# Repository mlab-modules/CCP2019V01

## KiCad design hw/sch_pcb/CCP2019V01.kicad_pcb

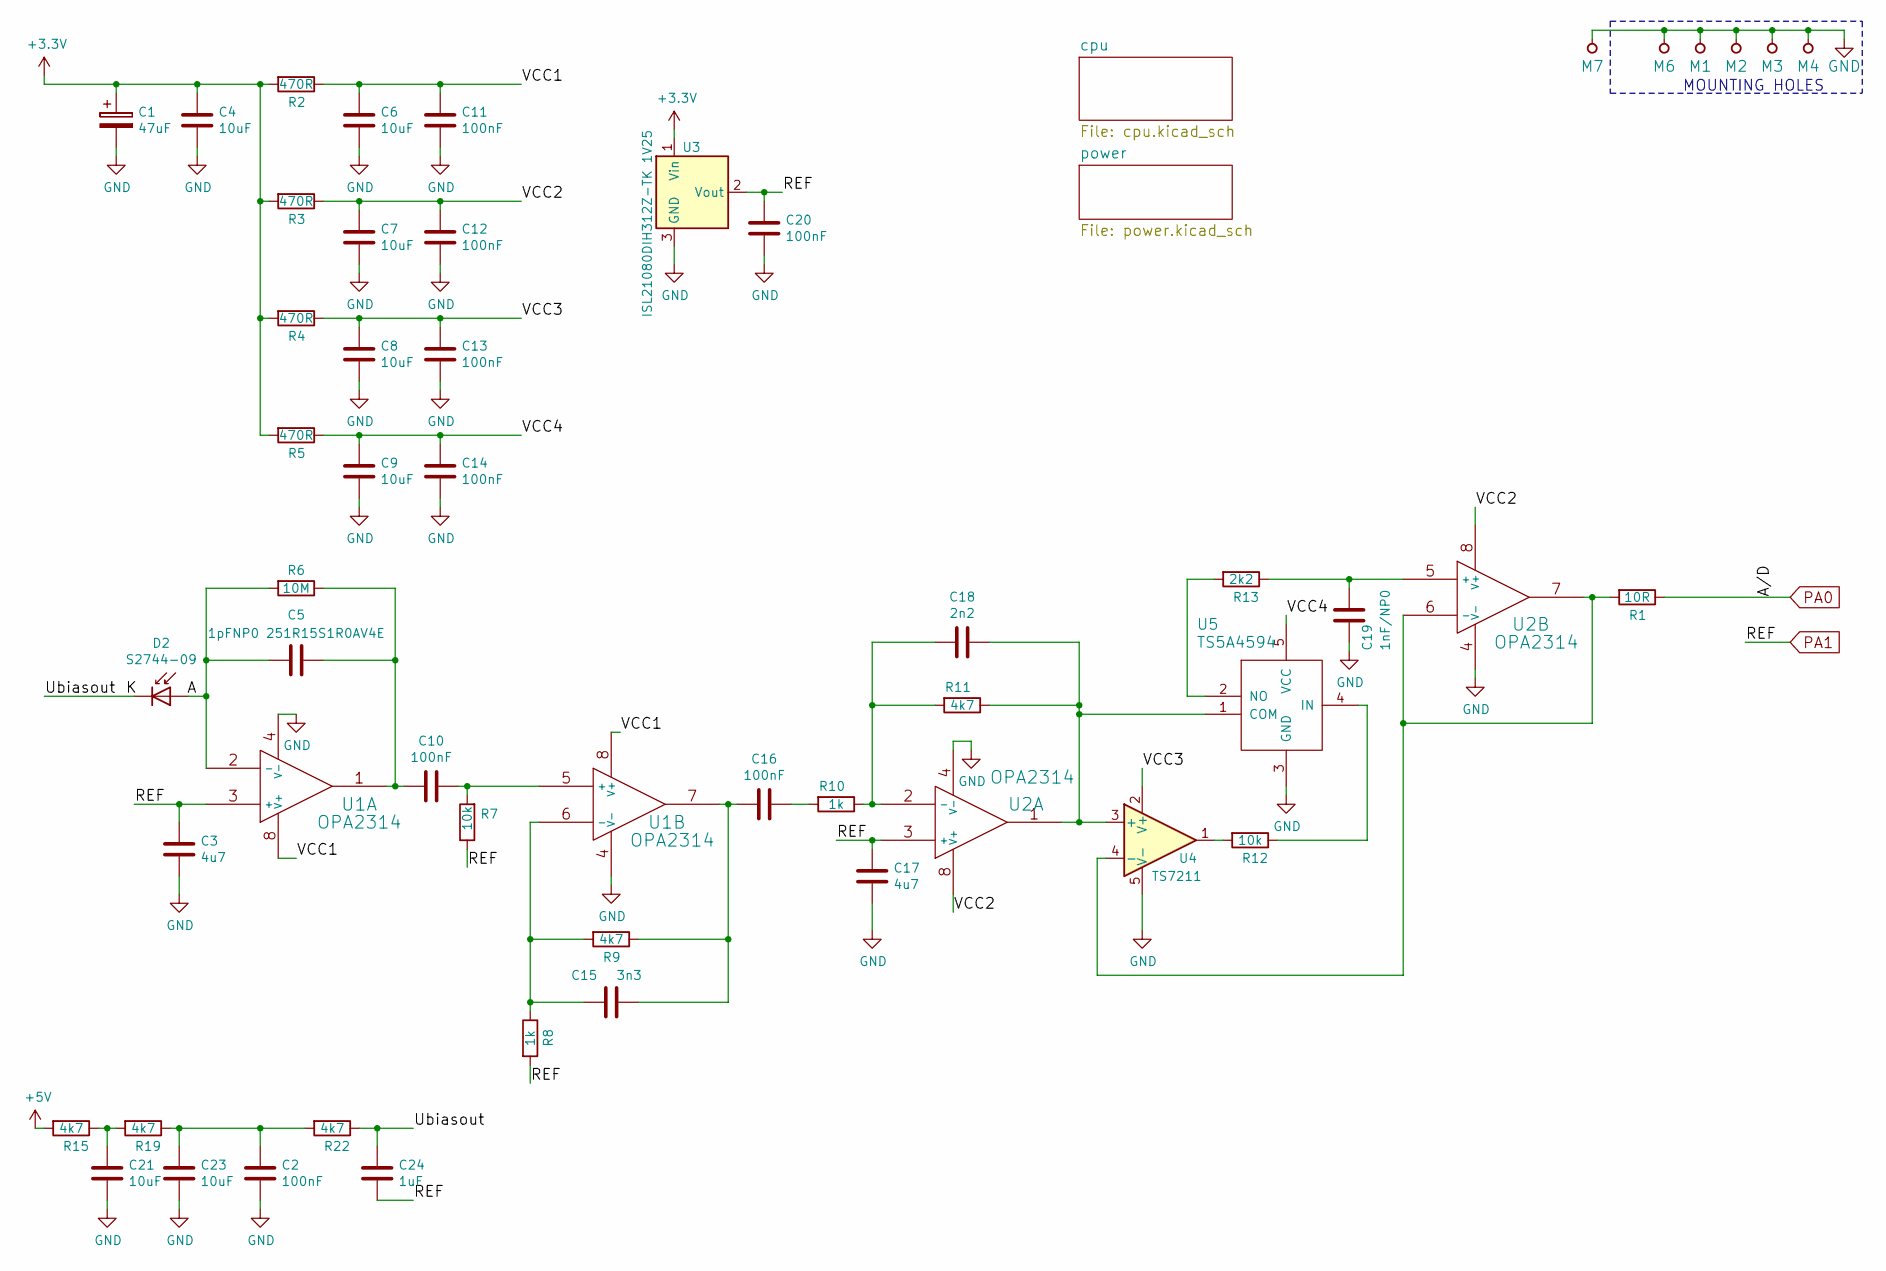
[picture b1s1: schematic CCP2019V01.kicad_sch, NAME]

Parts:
C1: 47uF; TantalC_SizeC_Reflow
C2, C10, C11, C12, C13, C14, C16, C20: 100nF; SMD-0805
C3, C17: 4u7; SMD-0805
C4, C6, C7, C8, C9, C21, C23: 10uF; SMD-0805
C5: 1pFNP0 251R15S1R0AV4E; SMD-0805
C15: 3n3; SMD-0805
C18: 2n2; SMD-0805
C19: 1nF/NP0; SMD-0805
C24: 1uF; SMD-0805
D2: S2744-09; HAMAMATSU_S2744-09
M1, M2, M3, M4: HOLE; MountingHole_3mm
M6, M7: BMI-S-210-F
R1: 10R; SMD-0805
R2, R3, R4, R5: 470R; SMD-0805
R6: 10M; SMD-0805
R7, R12: 10k; SMD-0805
R8, R10: 1k; SMD-0805
R9, R11, R15, R19, R22: 4k7; SMD-0805
R13: 2k2; SMD-0805
U1, U2: OPA2314; SOIC-8_3.9x4.9mm_Pitch1.27mm
U3: ISL21080DIH312Z-TK 1V25; SOT-23
U4: TS7211; SOT-23-5_HandSoldering
U5: TS5A4594; SOT-23-5_HandSoldering

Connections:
+3V3: C1.1, C4.1, R2.2, R3.2, R4.2, R5.2, U3.1 (Vin); also elsewhere on the board
+5V: R15.2; also elsewhere on the board
/A: C5.2, D2.2 (A), R6.2, U1.2 (-)
/K: C24.1, D2.1 (K), R22.1
/VCC1: C6.1, C11.1, R2.1, U1.8 (V+)
/VCC2: C7.1, C12.1, R3.1, U2.8 (V+)
/VCC3: C8.1, C13.1, R4.1, U4.2 (V+)
/VCC4: C9.1, C14.1, R5.1, U5.5 (VCC)
GND: C1.2, C2.2, C3.2, C4.2, C6.2, C7.2, C8.2, C9.2, C11.2, C12.2, C13.2, C14.2, C17.2, C19.2, C20.2, C21.2, C23.2, M1.1, M2.1, M3.1, M4.1, M6.1, M7.1, U1.4 (V-), U2.4 (V-), U3.3 (GND), U4.5 (V-), U5.3 (GND); also elsewhere on the board
unnamed: C2.1, C23.1, R19.1, R22.2
unnamed: C10.1, R7.2, U1.5 (+)
unnamed: C5.1, C10.2, R6.1, U1.1
unnamed: C15.1, C16.2, R9.1, U1.7
unnamed: C15.2, R8.1, R9.2, U1.6 (-)
unnamed: C16.1, R10.2
unnamed: C18.1, R11.1, U2.1, U4.3 (+), U5.1 (COM)
unnamed: C18.2, R10.1, R11.2, U2.2 (-)
unnamed: C19.1, R13.1, U2.5 (+)
unnamed: C21.1, R15.1, R19.2
unnamed: R1.2, U2.6 (-), U2.7, U4.4 (-)
unnamed: R12.1, U5.4 (IN)
unnamed: R12.2, U4.1
unnamed: R13.2, U5.2 (NO)
PA0: R1.1; also elsewhere on the board
PA1: C3.1, C17.1, C20.1, C24.2, R7.1, R8.2, U1.3 (+), U2.3 (+), U3.2 (Vout); also elsewhere on the board

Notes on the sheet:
MOUNTING HOLES

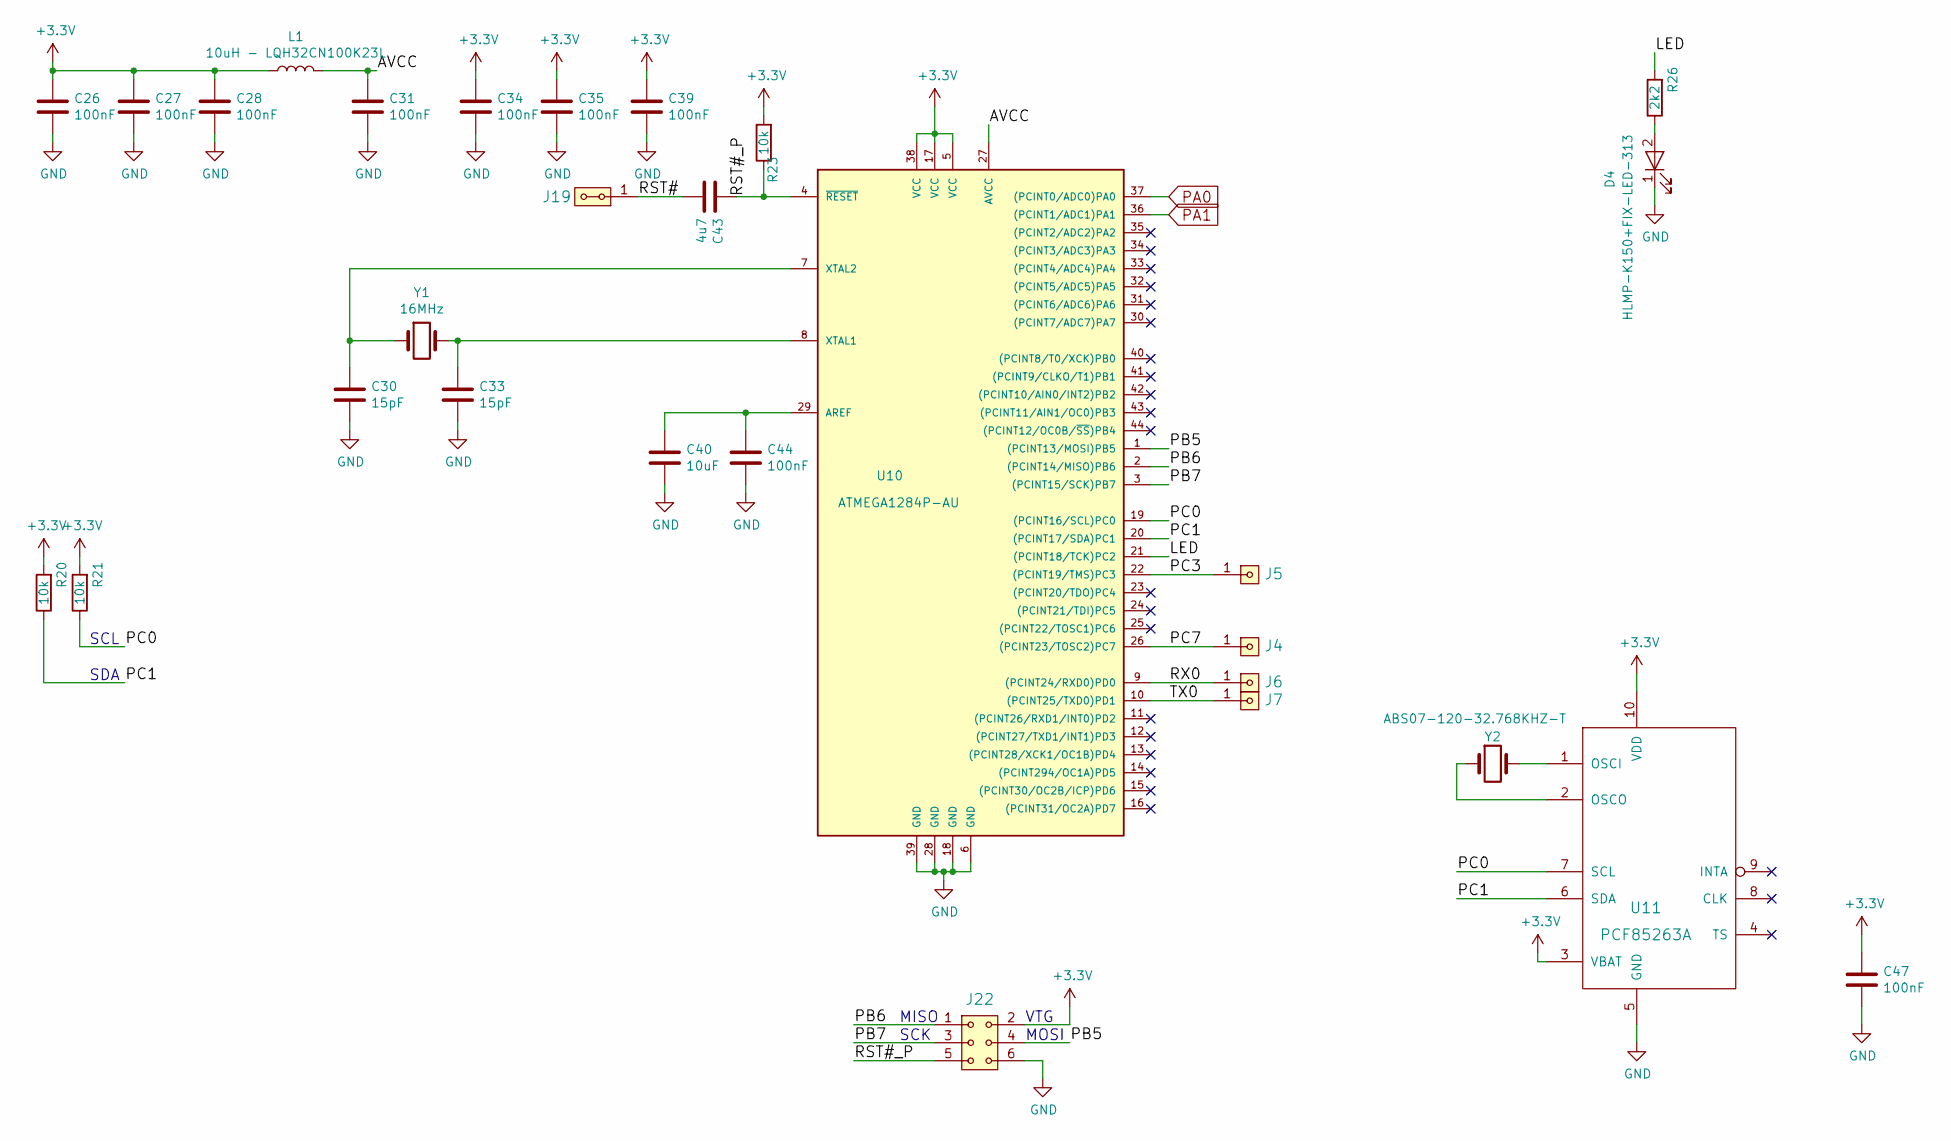
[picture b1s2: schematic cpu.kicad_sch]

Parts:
C26, C27, C28, C31, C34, C35, C39, C44, C47: 100nF; SMD-0805
C30, C33: 15pF; SMD-0805
C40: 10uF; SMD-0805
C43: 4u7; SMD-0805
D4: HLMP-K150+FIX-LED-313; LED_1206
J4, J5, J6, J7: HEADER_1x01; Straight_1x01
J19: HEADER_2x01_PARALLEL; Straight_2x01
J22: HEADER_2x03; Straight_2x03
L1: 10uH - LQH32CN100K23L; SMD-1210
R20, R21, R23: 10k; SMD-0805
R26: 2k2; SMD-0805
U10: ATMEGA1284P-AU; TQFP-44_10x10mm_P0.8mm
U11: PCF85263A; TSSOP-10_3x3mm_Pitch0.5mm
Y1: 16MHz; Crystal_HC49-U_Vertical
Y2: ABS07-120-32.768KHZ-T; ABS07

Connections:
+3V3: C26.1, C27.1, C28.1, C34.1, C35.1, C39.1, C47.1, J22.2, L1.1, R20.2, R21.2, R23.2, U10.5 (VCC), U10.17 (VCC), U10.38 (VCC), U11.3 (VBAT), U11.10 (VDD); also elsewhere on the board
/cpu/AVCC: C31.1, L1.2, U10.27 (AVCC)
/cpu/LED: R26.2, U10.21 ((PCINT18/TCK)PC2)
/cpu/PB5: J22.4, U10.1 ((PCINT13/MOSI)PB5)
/cpu/PB6: J22.1, U10.2 ((PCINT14/MISO)PB6)
/cpu/PB7: J22.3, U10.3 ((PCINT15/SCK)PB7)
/cpu/PC0: R21.1, U10.19 ((PCINT16/SCL)PC0), U11.7 (SCL)
/cpu/PC1: R20.1, U10.20 ((PCINT17/SDA)PC1), U11.6 (SDA)
/cpu/PC3: J5.1, U10.22 ((PCINT19/TMS)PC3)
/cpu/PC7: J4.1, U10.26 ((PCINT23/TOSC2)PC7)
/cpu/RST#: C43.2, J19.1, J19.2
/cpu/RST#_P: C43.1, J22.5, R23.1, U10.4 (~RESET)
/cpu/RX0: J6.1, U10.9 ((PCINT24/RXD0)PD0)
/cpu/TX0: J7.1, U10.10 ((PCINT25/TXD0)PD1)
GND: C26.2, C27.2, C28.2, C30.2, C31.2, C33.2, C34.2, C35.2, C39.2, C40.2, C44.2, C47.2, D4.1 (K), J22.6, U10.6 (GND), U10.18 (GND), U10.28 (GND), U10.39 (GND), U11.5 (GND); also elsewhere on the board
unnamed: C30.1, U10.7 (XTAL2), Y1.1
unnamed: C33.1, U10.8 (XTAL1), Y1.2
unnamed: C40.1, C44.1, U10.29 (AREF)
unnamed: D4.2 (A), R26.1
unnamed: U11.1 (OSCI), Y2.2
unnamed: U11.2 (OSCO), Y2.1
PA0: U10.37 ((PCINT0/ADC0)PA0); also elsewhere on the board
PA1: U10.36 ((PCINT1/ADC1)PA1); also elsewhere on the board

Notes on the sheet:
SDA
MISO
VTG
SCK
MOSI
SCL

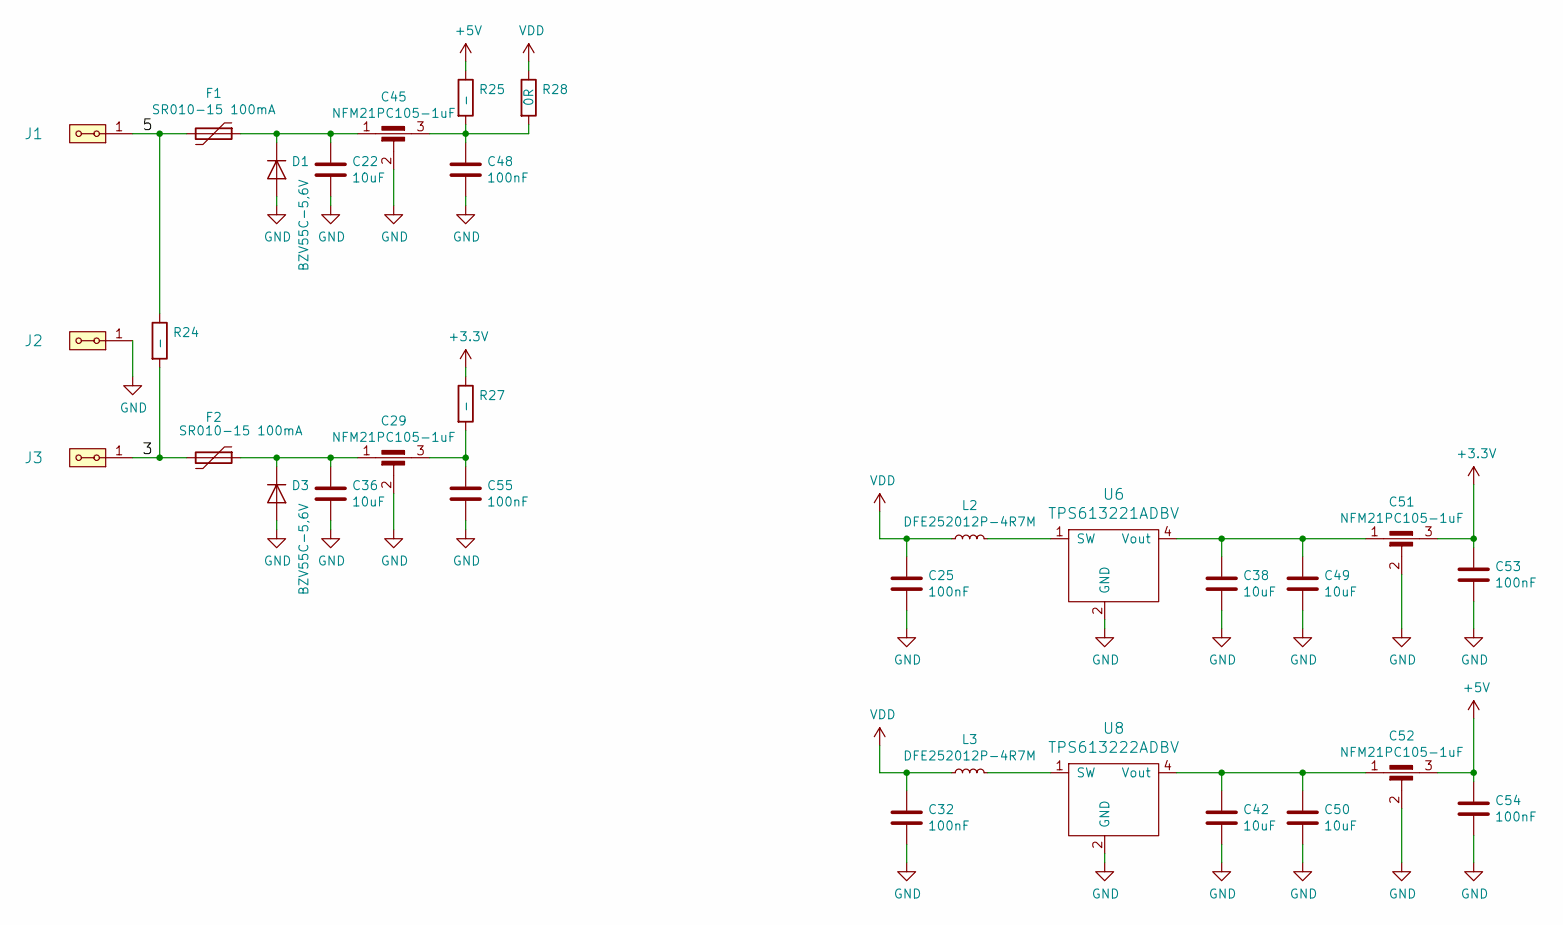
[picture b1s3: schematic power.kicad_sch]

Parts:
C22, C36, C38, C42, C49, C50: 10uF; SMD-0805
C25, C32, C48, C53, C54, C55: 100nF; SMD-0805
C29, C45, C51, C52: NFM21PC105-1uF; FIR1
D1, D3: BZV55C-5,6V; D_MiniMELF
F1, F2: SR010-15 100mA; SMD-0805
J1, J2, J3: HEADER_2x01_PARALLEL; Straight_1x02
L2, L3: DFE252012P-4R7M; R_0805_2012Metric_Pad1.15x1.40mm_HandSolder
R24, R25, R27: -; SMD-0805
R28: 0R; SMD-0805
U6: TPS613221ADBV; SOT-23-5
U8: TPS613222ADBV; SOT-23-5

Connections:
+3V3: C51.3, C53.1, R27.1; also elsewhere on the board
+5V: C52.3, C54.1, R25.1; also elsewhere on the board
/power/3: F2.2, J3.1, J3.2, R24.2
/power/5: F1.2, J1.1, J1.2, R24.1
GND: C22.2, C25.2, C29.2, C32.2, C36.2, C38.2, C42.2, C45.2, C48.2, C49.2, C50.2, C51.2, C52.2, C53.2, C54.2, C55.2, D1.2 (A), D3.2 (A), J2.1, J2.2, U6.2 (GND), U8.2 (GND); also elsewhere on the board
unnamed: C22.1, C45.1, D1.1 (K), F1.1
unnamed: C29.1, C36.1, D3.1 (K), F2.1
unnamed: C29.3, C55.1, R27.2
unnamed: C38.1, C49.1, C51.1, U6.4 (Vout)
unnamed: C42.1, C50.1, C52.1, U8.4 (Vout)
unnamed: C45.3, C48.1, R25.2, R28.2
unnamed: L2.2, U6.1 (SW)
unnamed: L3.2, U8.1 (SW)
VDD: C25.1, C32.1, L2.1, L3.1, R28.1

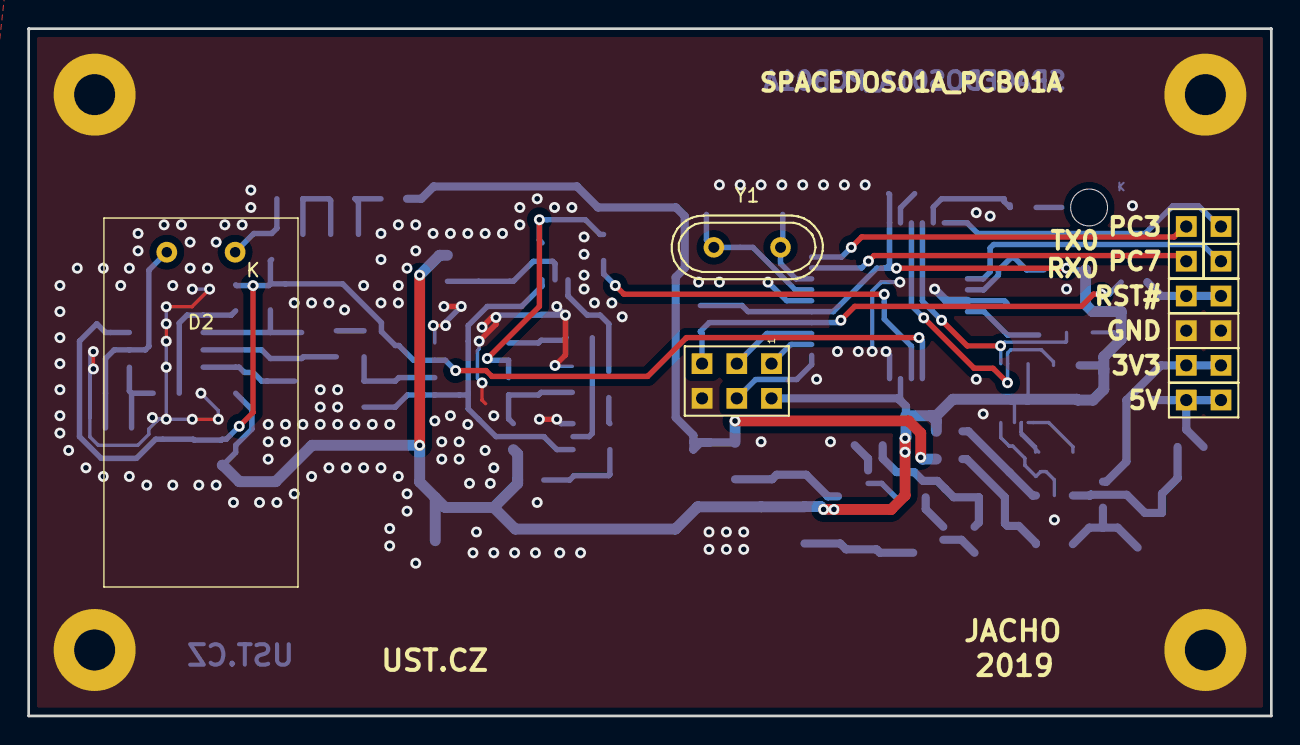
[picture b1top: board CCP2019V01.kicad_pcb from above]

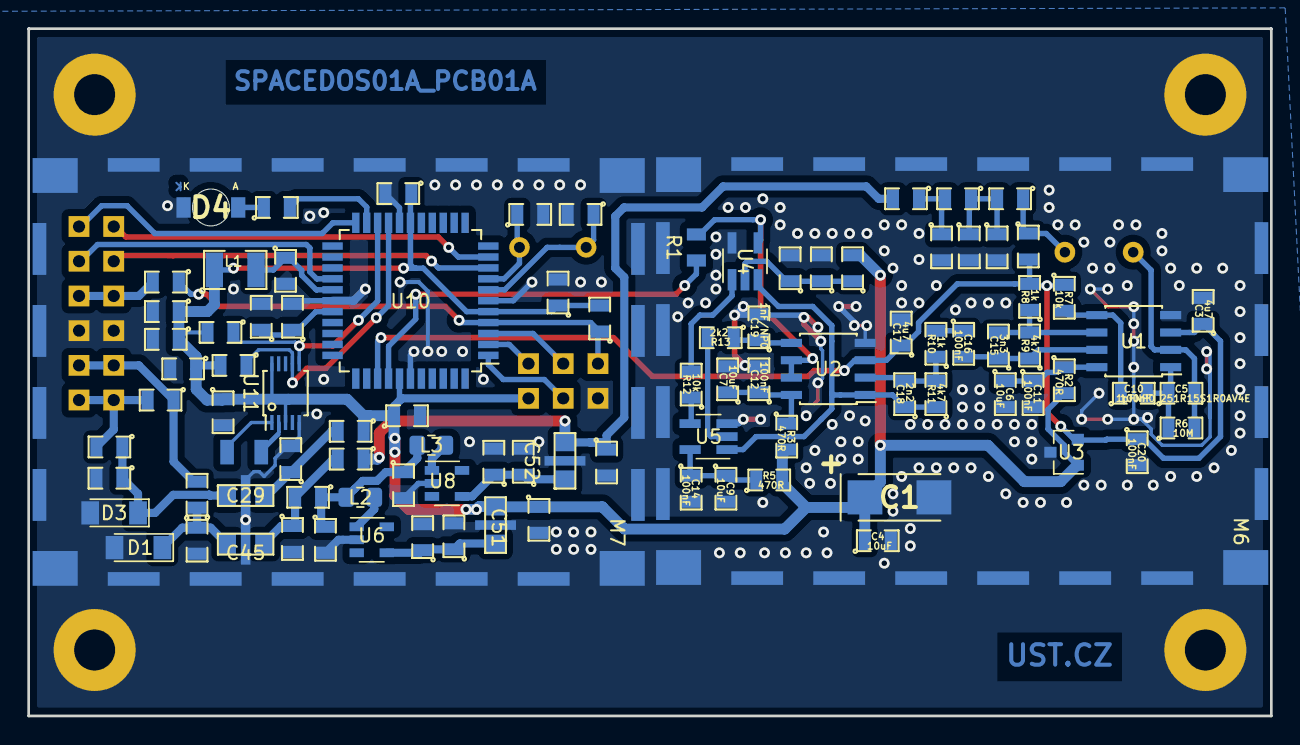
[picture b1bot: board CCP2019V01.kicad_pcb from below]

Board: 2 copper layers, 90.9 x 50.3 mm, 111 parts (96 on the bottom side), 55 nets.

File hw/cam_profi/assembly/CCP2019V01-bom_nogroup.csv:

Component,Description,Part,References,Value,Footprint,Quantity Per PCB,Datasheet
1,,C-device-DATALOGGER01A-rescue-CCP2019V01A-rescue,C30C33,15pF,SMD-0805,2,
2,Unpolarized capacitor,C,C18,2n2,SMD-0805,1,~
3,Unpolarized capacitor,C,C15,3n3,SMD-0805,1,~
4,Unpolarized capacitor,C,C2C10C11C12C13C14C16C20,100nF,SMD-0805,8,~
5,,C-device-DATALOGGER01A-rescue-CCP2019V01A-rescue,C25C26C27C28C31C32C34C35C39C44C47C48C53C54C55,100nF,SMD-0805,15,
6,Unpolarized capacitor,C,C24,1uF,SMD-0805,1,~
7,Unpolarized capacitor,C,C3C17,4u7,SMD-0805,2,~
8,,C-device-DATALOGGER01A-rescue-CCP2019V01A-rescue,C43,4u7,SMD-0805,1,
9,Unpolarized capacitor,C,C4C6C7C8C9C21C23,10uF,SMD-0805,7,~
10,,C-device-DATALOGGER01A-rescue-CCP2019V01A-rescue,C22C36C38C40C42C49C50,10uF,SMD-0805,7,
11,,CP-Device,C1,47uF,TantalC_SizeC_Reflow,1,
12,Unpolarized capacitor,C,C19,1nF/NP0,SMD-0805,1,~
13,Unpolarized capacitor,C,C5,1pFNP0 251R15S1R0AV4E,SMD-0805,1,~
14,,EMI_Filter_C-device-DATALOGGER01A-rescue-CCP2019V01A-rescue,C29C45C51C52,NFM21PC105-1uF,FIR1,4,http://www.murata.com/~/media/webrenewal/support/library/cat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
15,,D-device-DATALOGGER01A-rescue-CCP2019V01A-rescue,D1D3,"BZV55C-5,6V",D_MiniMELF,2,
16,,LED-device-DATALOGGER01A-rescue-CCP2019V01A-rescue,D4,HLMP-K150+FIX-LED-313,LED_1206,1,
17,Photodiode,D_Photo,D2,S2744-09,HAMAMATSU_S2744-09,1,~
18,,Polyfuse-device-DATALOGGER01A-rescue-CCP2019V01A-rescue,F1F2,SR010-15 100mA ,SMD-0805,2,
19,,HEADER_1x01-MLAB_HEADER,J4J5J6J7,HEADER_1x01,Straight_1x01,4,
20,,HEADER_2x01_PARALLEL-MLAB_HEADER,J1J2J3,HEADER_2x01_PARALLEL,Straight_1x02,3,
21,,HEADER_2x01_PARALLEL-MLAB_HEADER,J19,HEADER_2x01_PARALLEL,Straight_2x01,1,
22,,HEADER_2x03-MLAB_HEADER,J22,HEADER_2x03,Straight_2x03,1,
23,,L-device-DATALOGGER01A-rescue-CCP2019V01A-rescue,L1,10uH - LQH32CN100K23L,SMD-1210,1,
24,"Inductor, small symbol",L_Small,L2L3,DFE252012P-4R7M,R_0805_2012Metric_Pad1.15x1.40mm_HandSolder,2,~
25,,HOLE-MLAB_MECHANICAL,M6M7,BMI-S-210-F,BMI-S-210-F,2,
26,Resistor,R,R28,0R,SMD-0805,1,~
27,Resistor,R,R1,10R,SMD-0805,1,~
28,Resistor,R,R2R3R4R5,470R,SMD-0805,4,~
29,Resistor,R,R8R10,1k,SMD-0805,2,~
30,Resistor,R,R13,2k2,SMD-0805,1,~
31,,R-device-DATALOGGER01A-rescue-CCP2019V01A-rescue,R26,2k2,SMD-0805,1,
32,Resistor,R,R9R11R15R19R22,4k7,SMD-0805,5,~
33,Resistor,R,R7R12,10k,SMD-0805,2,~
34,,R-device-DATALOGGER01A-rescue-CCP2019V01A-rescue,R20R21R23,10k,SMD-0805,3,
35,Resistor,R,R6,10M,SMD-0805,1,~
36,Resistor,R,R24R25R27,-,SMD-0805,3,~
37,,ATMEGA1284P-AU-atmel-DATALOGGER01A-rescue-CCP2019V01A-rescue,U10,ATMEGA1284P-AU,TQFP-44_10x10mm_P0.8mm,1,http://www.atmel.com/Images/Atmel-8272-8-bit-AVR-microcontro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
38,"2.0V 25μA Micropower Voltage Reference, SOT-23",ISL21070CIH320Z-TK,U3,ISL21080DIH312Z-TK  1V25,SOT-23,1,http://www.intersil.com/content/dam/Intersil/documents/fn75/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
39,,AD8692-MLAB_IO,U1U2,OPA2314,SOIC-8_3.9x4.9mm_Pitch1.27mm,2,
40,,PCF85263A-MLAB_IO,U11,PCF85263A,TSSOP-10_3x3mm_Pitch0.5mm,1,
41,,TPS61322xA-MLAB_IO,U6,TPS613221ADBV,SOT-23-5,1,
42,,TPS61322xA-MLAB_IO,U8,TPS613222ADBV,SOT-23-5,1,
43,,TS5A4594-MLAB_IO,U5,TS5A4594,SOT-23-5_HandSoldering,1,
44,"Single Rail-to-Rail High Output Current Operational Amplifiers, SOT-23-5",OP179GRT,U4,TS7211,SOT-23-5_HandSoldering,1,http://www.analog.com/media/en/technical-documentation/data-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
45,Two pin crystal,Crystal,Y1,16MHz,Crystal_HC49-U_Vertical,1,~
46,,Crystal-device-DATALOGGER01A-rescue-CCP2019V01A-rescue,Y2,ABS07-120-32.768KHZ-T,ABS07,1,

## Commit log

2023-04-01 Adding force option to enable splitting in not fresh copy of Modules repository.
2023-05-28 automated commit; add github actions
2023-05-28 Update metadata files
2023-06-15 Update workflow files
2023-07-05 automated commit; rename source files to new naming convence
2023-09-16 Update status
2024-07-06 Convert to KiCADv7 project.
2024-07-06 Activate updated workflow.
2024-07-06 Update actions products
2026-02-14 Update metadata.yaml
    Make the design outdated.
